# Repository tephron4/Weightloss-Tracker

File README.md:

# Weightloss-Tracker

Arduino project for tracking weight loss progress with LEDs

## Weight Tracker Controller (weight-tracker.ino)

Logic for arduino to recieve weight values over bluetooth.

## Web Application (web-app.html)

Web application for connecting to the arduino (via bluetooth), entering weight values, and sending the values to the arduino.p

## Led Controller (led-controller.ino)

Contains logic for controlling the onboard LED on the arduino. This is used to test the bluetooth connection to the arduino.

## Web Controller (web-controller.html)

Web app that handles sending values to the arduino over bluetooth.

## Bill of Materials and Schematic

This project uses:

### BOM

| Part               | Count |
| ------------------ | ----- |
| Arduino Nano ESP32 | 1     |
| SN74HC595N         | 1     |
| 5mm LED - Red      | 5     |
| 5mm LED - Yellow   | 2     |
| 5mm LED - Green    | 2     |
| 220-ohm Resistor   | 8     |

### Schematic

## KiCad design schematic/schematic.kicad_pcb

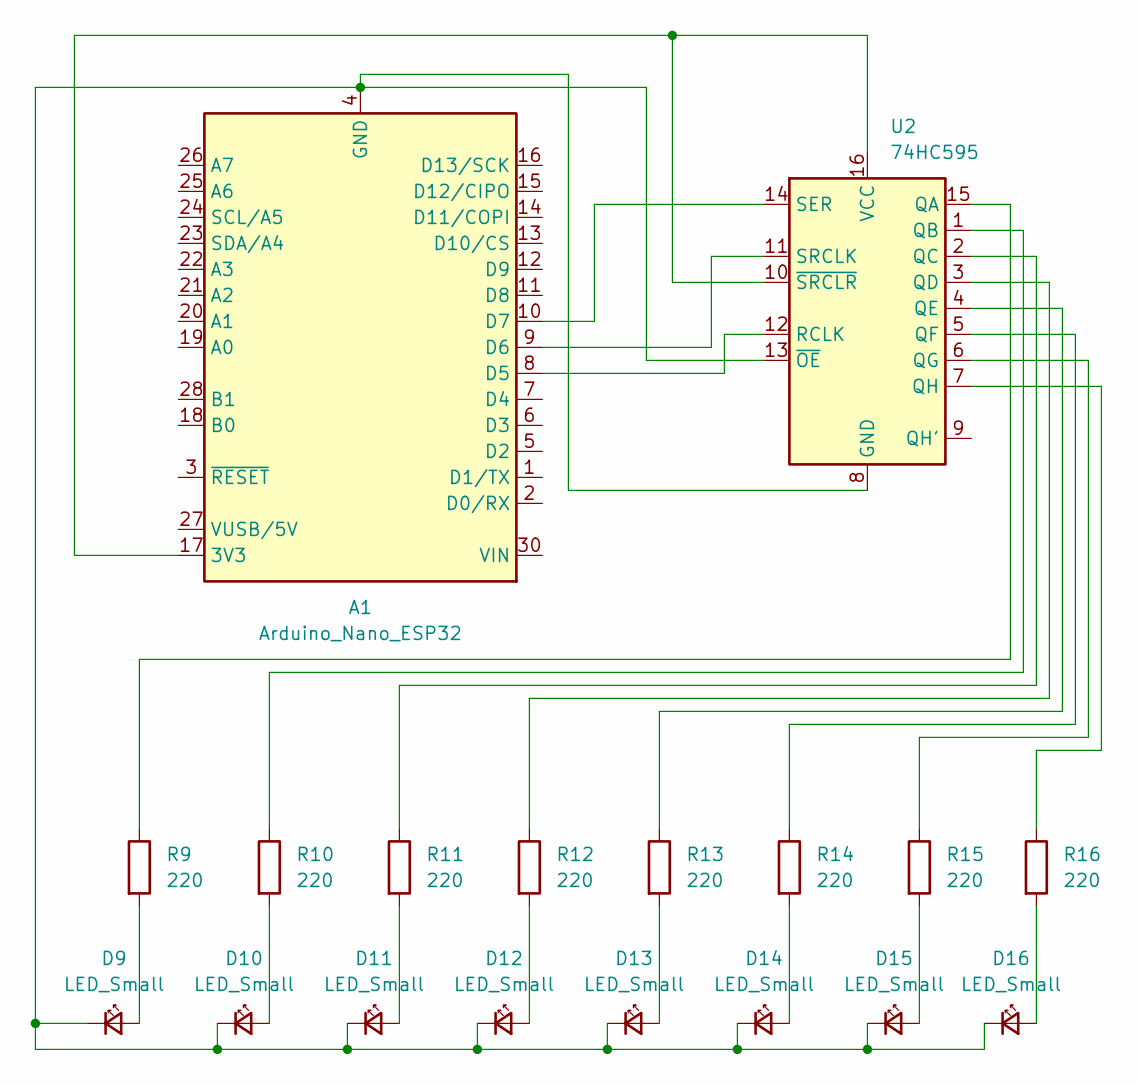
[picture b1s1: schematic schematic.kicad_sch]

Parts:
A1: Arduino_Nano_ESP32; Arduino_Nano
D9, D10, D11, D12, D13, D14, D15, D16: LED_Small; LED_D5.0mm
R9, R10, R11, R12, R13, R14, R15, R16: 220; R_Axial_DIN0207_L6.3mm_D2.5mm_P7.62mm_Horizontal
U2: 74HC595; DIP-16_W7.62mm

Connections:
unnamed: A1.17 (3V3), U2.10 (~SRCLR), U2.16 (VCC)
unnamed: A1.8 (D5), U2.12 (RCLK)
unnamed: A1.9 (D6), U2.11 (SRCLK)
unnamed: A1.10 (D7), U2.14 (SER)
unnamed: D9.2 (A), R9.2
unnamed: D10.2 (A), R10.2
unnamed: A1.4 (GND), A1.29 (GND), D9.1 (K), D10.1 (K), D11.1 (K), D12.1 (K), D13.1 (K), D14.1 (K), D15.1 (K), D16.1 (K), U2.8 (GND), U2.13 (~OE)
unnamed: D11.2 (A), R11.2
unnamed: D12.2 (A), R12.2
unnamed: D13.2 (A), R13.2
unnamed: D14.2 (A), R14.2
unnamed: D15.2 (A), R15.2
unnamed: D16.2 (A), R16.2
unnamed: R9.1, U2.15 (QA)
unnamed: R10.1, U2.1 (QB)
unnamed: R11.1, U2.2 (QC)
unnamed: R12.1, U2.3 (QD)
unnamed: R13.1, U2.4 (QE)
unnamed: R14.1, U2.5 (QF)
unnamed: R15.1, U2.6 (QG)
unnamed: R16.1, U2.7 (QH)

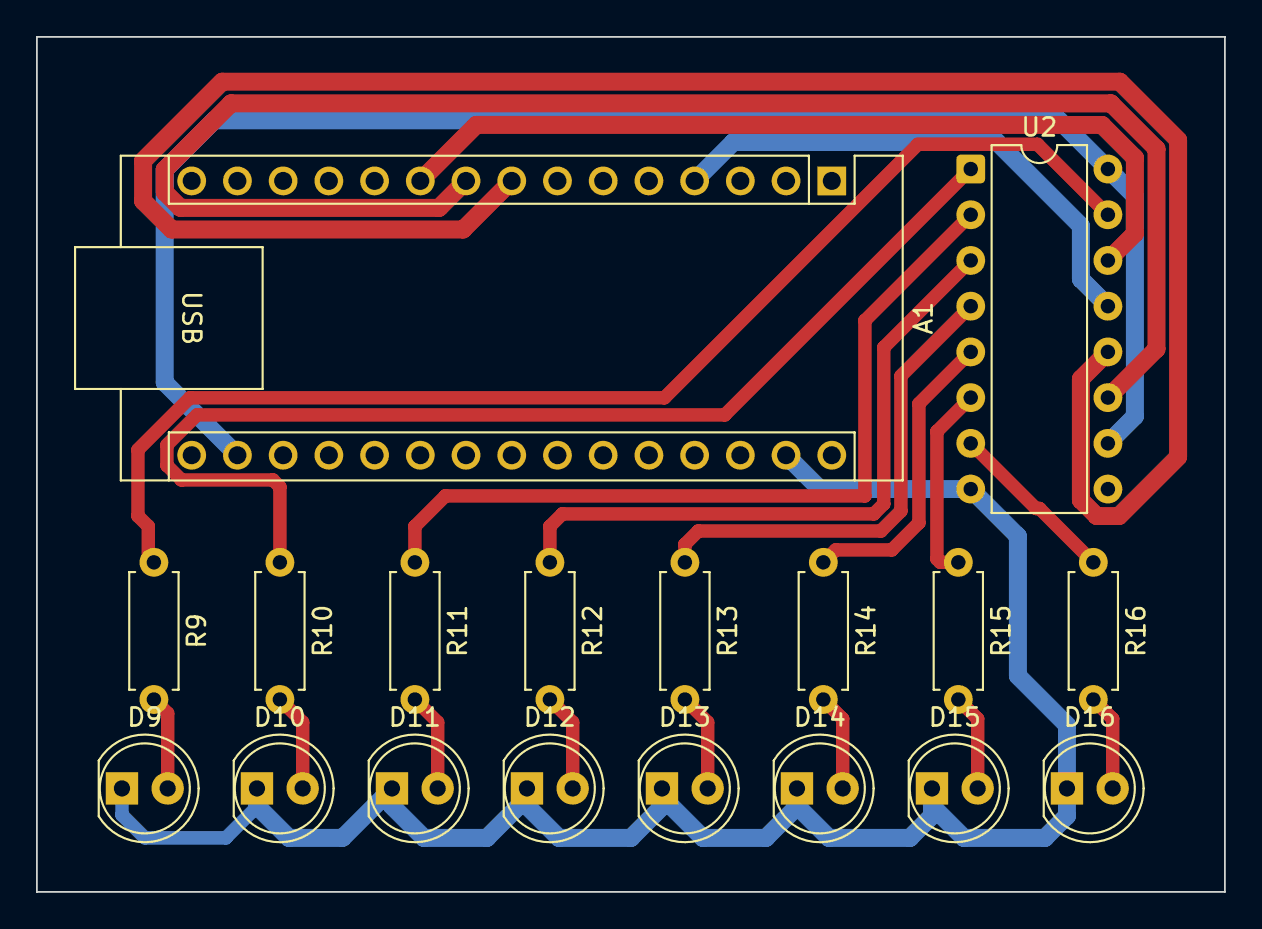
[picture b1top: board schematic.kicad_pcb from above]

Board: 2 copper layers, 66.0 x 47.5 mm, 18 parts (0 on the bottom side), 21 nets.

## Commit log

2026-03-18 Add preliminary led-controller and web-controller
    Add initial led-controller.ino and web-controller.html, and update README.md to document the new examples.
2026-03-18 Added new files: web-app.html and weight-tracker.ino, and updated README.md with project details.
2026-03-18 Fix bluetooth filter name to match the device name used in the NanoESP32 code.
2026-03-18 Add logic for saving and resetting weights in the web app, and ensure the BLE service has a reset characteristic.
    This allows users to clear all saved data if they want to start fresh. Also added a safety check to prevent sending negative weights.
2026-03-18 Add led controls and progress tracking.
2026-03-18 Fix visual of web app.
2026-03-18 Reload progress on new send actions.
2026-03-20 Add BOM and schematic
2026-04-24 Update schematic and swap pins for simplification
2026-04-24 Fix PCB board setup
2026-04-24 Add files for ordering a PCB
2026-04-25 Create files for ordering pcb (with zip)
2026-04-26 Add outline to pcb
2026-05-05 Update schematic to use correct, non-surface mount resistors
